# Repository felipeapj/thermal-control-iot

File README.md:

# thermal-control-iot

Its a project to control TECs (Thermoelectric Coolers) using a Node MCU module.

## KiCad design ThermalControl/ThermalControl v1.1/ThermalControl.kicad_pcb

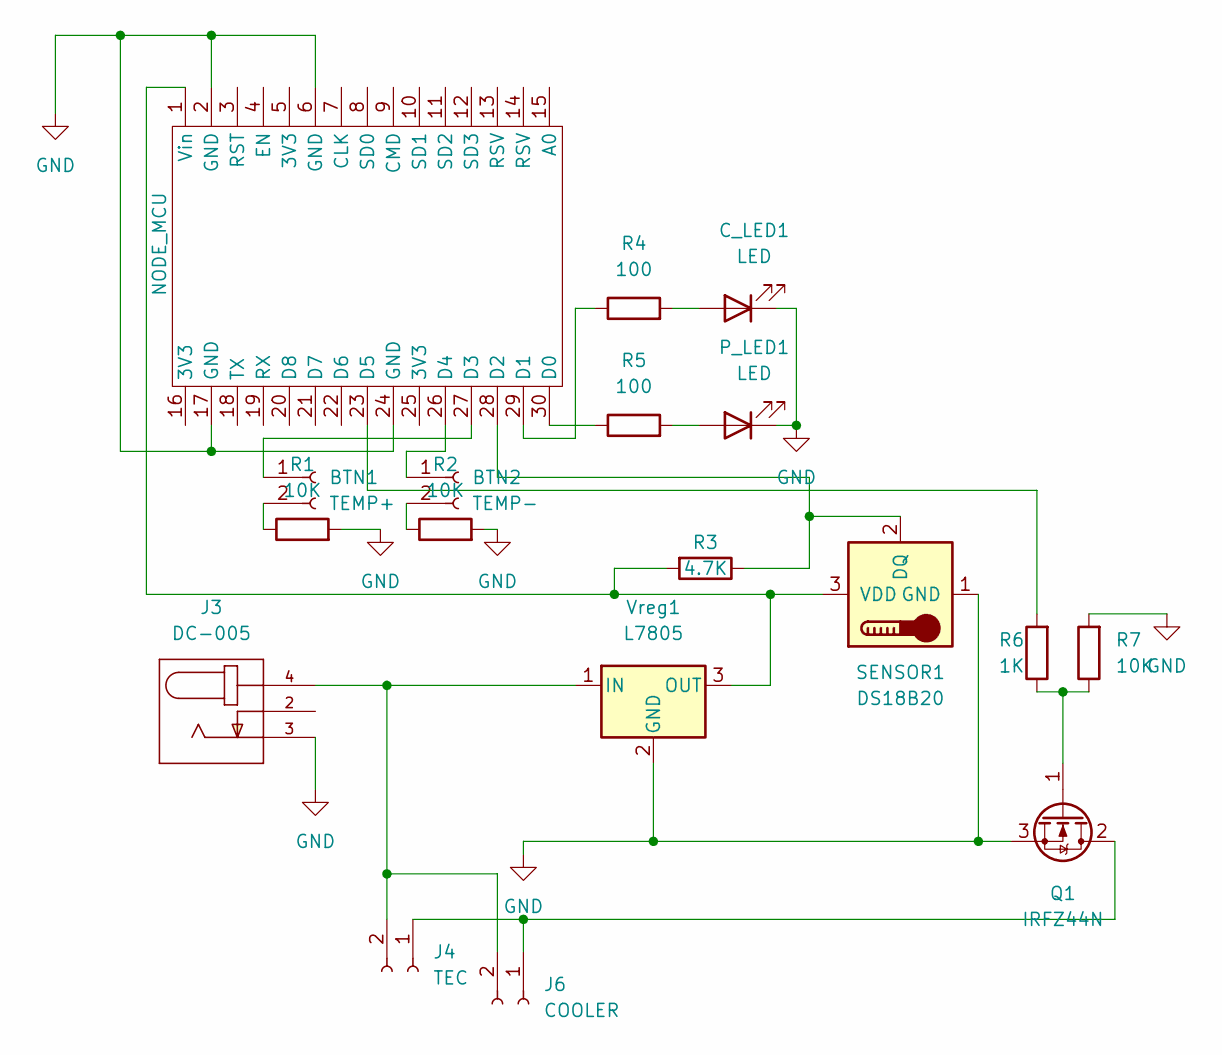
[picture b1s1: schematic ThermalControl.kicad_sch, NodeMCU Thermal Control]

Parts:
BTN1: TEMP+; PinSocket_1x02_P2.54mm_Vertical
BTN2: TEMP-; PinSocket_1x02_P2.54mm_Vertical
C_LED1: LED; LED_D5.0mm
J3: DC-005
J4: TEC; SolderWire-0.5sqmm_1x02_P4.8mm_D0.9mm_OD2.3mm
J6: COOLER; SolderWire-0.5sqmm_1x02_P4.8mm_D0.9mm_OD2.3mm
P_LED1: LED; LED_D5.0mm
Q1: IRFZ44N; TO-220-3_Vertical
R1, R2, R7: 10K; R_Axial_DIN0207_L6.3mm_D2.5mm_P7.62mm_Horizontal
R3: 4.7K; R_Axial_DIN0207_L6.3mm_D2.5mm_P7.62mm_Horizontal
R4, R5: 100; R_Axial_DIN0207_L6.3mm_D2.5mm_P7.62mm_Horizontal
R6: 1K; R_Axial_DIN0207_L6.3mm_D2.5mm_P7.62mm_Horizontal
SENSOR1: DS18B20; TO-92_Wide
U1: NODE_MCU; node_mcu_socket
Vreg1: L7805; TO-220-3_Vertical

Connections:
GND: C_LED1.1 (K), J3.3, P_LED1.1 (K), Q1.3 (S), R1.2, R2.2, R7.2, SENSOR1.1 (GND), U1.2 (GND), U1.6 (GND), U1.17 (GND), U1.24 (GND), Vreg1.2 (GND)
unnamed: BTN1.1, U1.27 (D3)
unnamed: BTN1.2, R1.1
unnamed: BTN2.1, U1.26 (D4)
unnamed: BTN2.2, R2.1
unnamed: J3.4, J4.2, J6.2, Vreg1.1 (IN)
unnamed: J4.1, J6.1, Q1.2 (D)
unnamed: Q1.1 (G), R6.1, R7.1
unnamed: R3.1, SENSOR1.2 (DQ), U1.28 (D2)
unnamed: R3.2, SENSOR1.3 (VDD), U1.1 (Vin), Vreg1.3 (OUT)
unnamed: C_LED1.2 (A), R4.2
unnamed: R5.1, U1.30 (D0)
unnamed: P_LED1.2 (A), R5.2
unnamed: R6.2, U1.23 (D5)
unnamed: R4.1, U1.29 (D1)

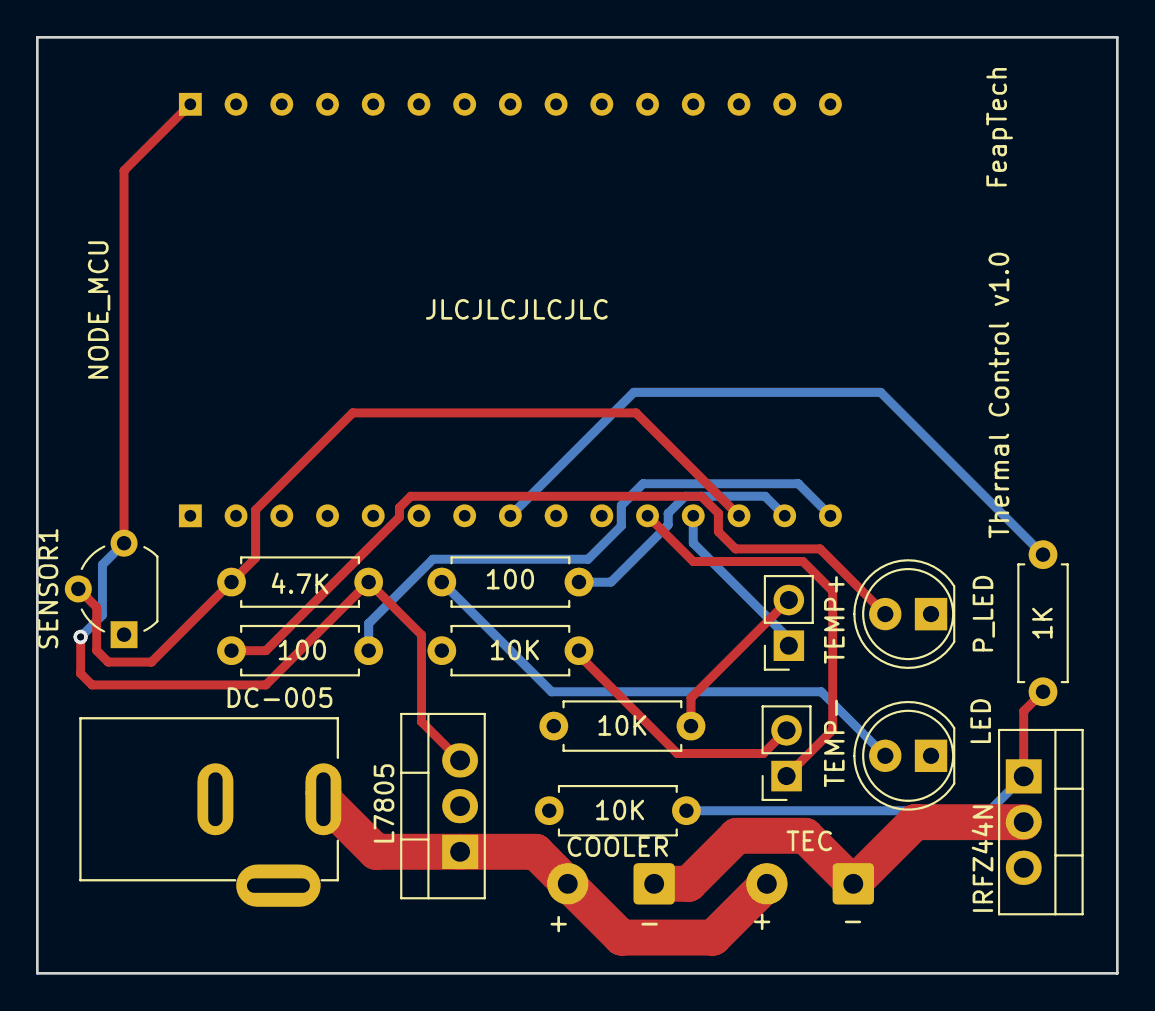
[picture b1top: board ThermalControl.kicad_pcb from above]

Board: 2 copper layers, 60.0 x 52.0 mm, 18 parts (0 on the bottom side), 15 nets.

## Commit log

2022-03-19 project ready to production
2022-03-19 changed relay to mosfet
2022-04-08 schematic versions
